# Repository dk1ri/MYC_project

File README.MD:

#The MYC Project 

MYC is a universal system to control hardware and software. A MYC system can merge different IOT systems and programms using a common user interface.

A MYC system contains skins and funcs (and a few other components)

A skin is a user interface, which can be selected and configured by the user - or a remote control or a simple switch.

A func is something, what can be controlled as a device or a program.

skin + func = App (or something similar)

The connection between skin and func is done by the (OSI layer 7) MYC protocol. The other OSI layer can be selected by demand.

MYC is not ready, you are invited to contribute

See also www.dk1ri.de

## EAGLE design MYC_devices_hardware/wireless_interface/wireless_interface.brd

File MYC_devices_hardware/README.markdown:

#MYC Hardware

Here some MYC hardware device are described.

All of them understand the MYC protocol. Some can be use a standalone equipment as well

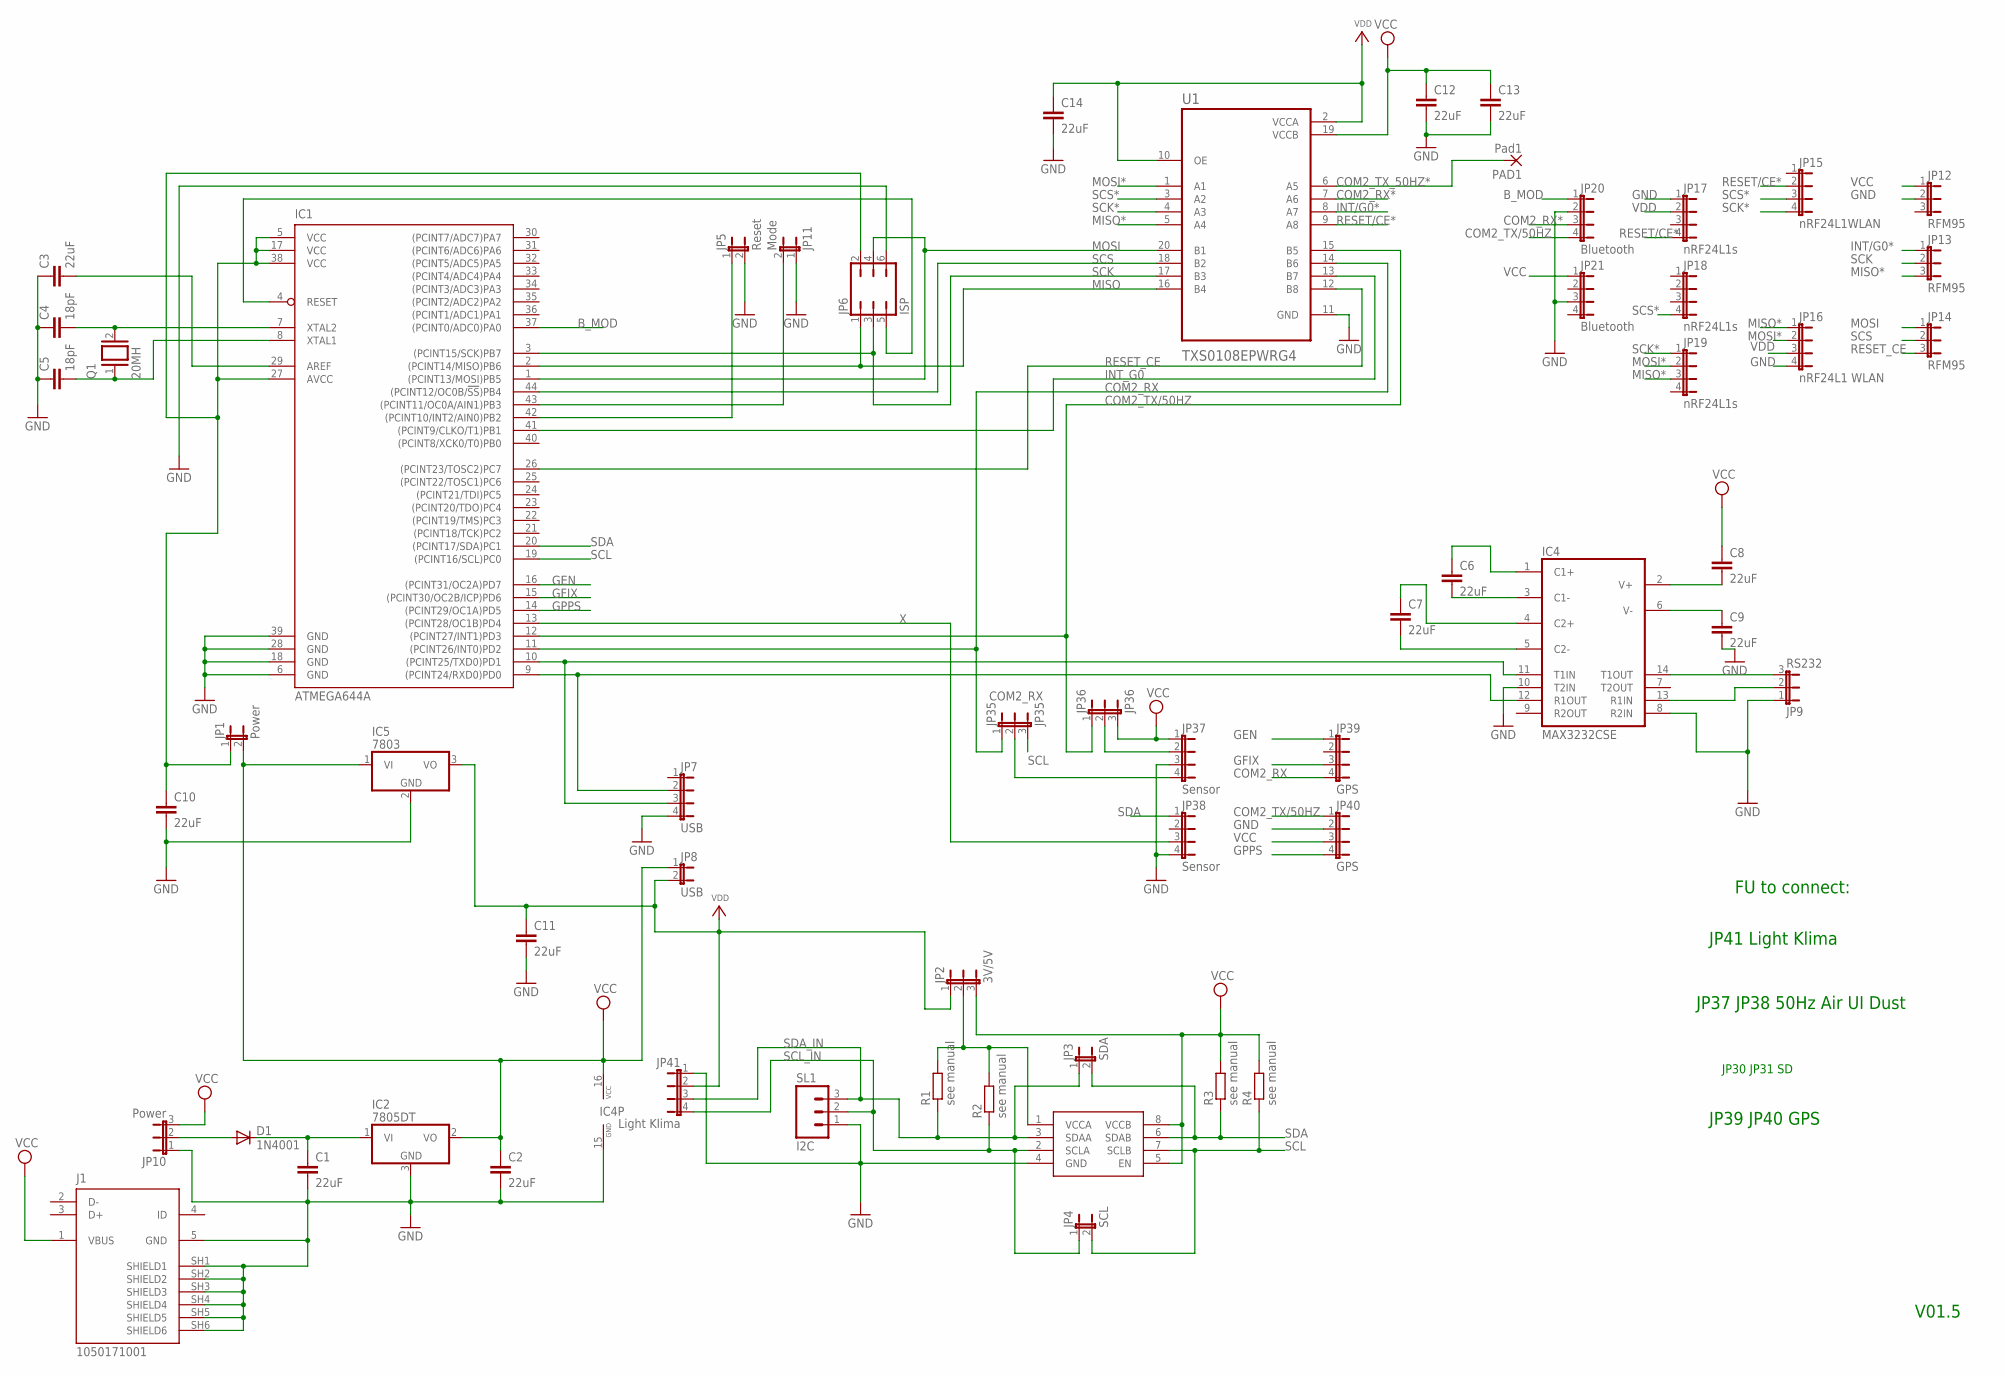
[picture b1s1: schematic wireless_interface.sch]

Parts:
C1, C2, C3, C6, C7, C8, C9, C10, C11, C12, C13, C14: 22uF; C1206
C4, C5: 18pF; C025-025X050
D1: 1N4001; SOD106-W
IC1: ATMEGA644A; TQFP44
IC2: 7805DT; TO252
IC3: PCA9517; SO-08
IC4: MAX3232CSE; SO16
IC5: 7803; TO220V
J1: 1050171001; MOLEX_1050171001
JP1: Power; JP1
JP2: 3V/5V; JP2
JP3: SDA; JP1
JP4: SCL; JP1
JP5: Reset; JP1
JP6: ISP; JP3Q
JP7: USB; JP4
JP8: USB; JP1
JP9: RS232; JP2
JP10: Power; JP2
JP11: Mode; JP1
JP12, JP13, JP14: RFM95; JP2
JP15: nRF24L1WLAN; JP4
JP16: nRF24L1 WLAN; JP4
JP17, JP18, JP19: nRF24L1s; JP4
JP20, JP21: Bluetooth; JP4
JP35: JP35; JP2
JP36: JP36; JP2
JP37, JP38: Sensor; JP4
JP39, JP40: GPS; JP4
JP41: Light Klima; JP4
PAD1: Pad1; SMD1,27-2,54
Q1: 20MH; QS
R1, R2, R3, R4: see manual; R1206
SL1: I2C; 03P
U1: TXS0108EPWRG4; SOP65P640X120-20N

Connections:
B_MOD: IC1.37 ((PCINT0/ADC0)PA0), JP20.1
COM2_RX: IC1.11 ((PCINT26/INT0)PD2), JP35.1, JP39.4, U1.14 (B6)
COM2_RX*: JP20.3, U1.7 (A6)
COM2_TX/50HZ: IC1.12 ((PCINT27/INT1)PD3), JP20.4, JP36.1, JP40.1, U1.15 (B5)
COM2_TX_50HZ*: PAD1.1, U1.6 (A5)
GEN: IC1.16 ((PCINT31/OC2A)PD7), JP39.1
GFIX: IC1.15 ((PCINT30/OC2B/ICP)PD6), JP39.3
GND: C1.2, C2.2, C3.1, C4.1, C5.1, C9.2, C10.2, C11.2, C12.2, C13.2, C14.2, IC1.6 (GND), IC1.18 (GND), IC1.28 (GND), IC1.39 (GND), IC2.3 (GND), IC3.4 (GND), IC4.8 (R2IN), IC4.10 (T2IN), IC4.15 (GND), IC5.2 (GND), J1.5 (GND), J1.SH1 (SHIELD1), J1.SH2 (SHIELD2), J1.SH3 (SHIELD3), J1.SH4 (SHIELD4), J1.SH5 (SHIELD5), J1.SH6 (SHIELD6), JP5.2, JP6.6, JP7.4, JP9.1, JP10.1, JP11.1, JP12.2, JP16.4, JP17.1, JP20.2, JP21.3, JP37.3, JP38.4, JP40.2, JP41.1, SL1.1, U1.11 (GND)
GPPS: IC1.14 ((PCINT29/OC1A)PD5), JP40.4
INT/G0*: JP13.1, U1.8 (A7)
INT_G0: IC1.41 ((PCINT9/CLKO/T1)PB1), U1.13 (B7)
MISO: IC1.2 ((PCINT14/MISO)PB6), JP6.1, U1.16 (B4)
MISO*: JP13.3, JP16.1, JP19.3, U1.5 (A4)
MOSI: IC1.1 ((PCINT13/MOSI)PB5), JP6.4, JP14.1, U1.20 (B1)
MOSI*: JP16.2, JP19.2, U1.1 (A1)
unnamed: JP36.2, JP37.2
unnamed: C10.1, IC1.5 (VCC), IC1.17 (VCC), IC1.27 (AVCC), IC1.38 (VCC), JP1.1, JP6.2
unnamed: IC4.13 (R1IN), JP9.2
unnamed: IC1.9 ((PCINT24/RXD0)PD0), IC4.12 (R1OUT), JP7.2
unnamed: IC1.42 ((PCINT10/INT2/AIN0)PB2), JP5.1
unnamed: IC1.43 ((PCINT11/OC0A/AIN1)PB3), JP11.2
unnamed: C6.1, IC4.1 (C1+)
unnamed: C6.2, IC4.3 (C1-)
unnamed: C7.1, IC4.4 (C2+)
unnamed: C7.2, IC4.5 (C2-)
unnamed: D1.A, JP10.2
unnamed: C8.2, IC4.2 (V+)
unnamed: C3.2, IC1.29 (AREF)
unnamed: C9.1, IC4.6 (V-)
unnamed: IC4.14 (T1OUT), JP9.3
unnamed: JP35.2, JP37.4
unnamed: IC1.4 (RESET), JP6.5
unnamed: C4.2, IC1.7 (XTAL2), Q1.2
unnamed: IC1.10 ((PCINT25/TXD0)PD1), IC4.11 (T1IN), JP7.3
unnamed: C1.1, D1.C, IC2.1 (VI)
unnamed: C5.2, IC1.8 (XTAL1), Q1.1
unnamed: IC3.1 (VCCA), JP2.2, R1.2, R2.2
RESET/CE*: JP15.2, JP17.4, U1.9 (A8)
RESET_CE: IC1.26 ((PCINT23/TOSC2)PC7), JP14.3, U1.12 (B8)
SCK: IC1.3 ((PCINT15/SCK)PB7), JP6.3, JP13.2, U1.17 (B3)
SCK*: JP15.4, JP19.1, U1.4 (A3)
SCL: IC1.19 ((PCINT16/SCL)PC0), IC3.7 (SCLB), JP4.2, JP35.3, R4.1
SCL_IN: IC3.2 (SCLA), JP4.1, JP41.4, R2.1, SL1.2
SCS: IC1.44 ((PCINT12/OC0B/!SS!)PB4), JP14.2, U1.18 (B2)
SCS*: JP15.3, JP18.4, U1.3 (A2)
SDA: IC1.20 ((PCINT17/SDA)PC1), IC3.6 (SDAB), JP3.2, JP38.1, R3.1
SDA_IN: IC3.3 (SDAA), JP3.1, JP41.3, R1.1, SL1.3
VCC: C2.1, C8.1, C12.1, C13.1, IC2.2 (VO), IC3.5 (EN), IC3.8 (VCCB), IC4.16 (VCC), IC5.1 (VI), J1.1 (VBUS), JP1.2, JP2.3, JP8.1, JP10.3, JP12.1, JP21.1, JP36.3, JP37.1, JP40.3, R3.2, R4.2, U1.19 (VCCB)
VDD: C11.1, C14.1, IC5.3 (VO), JP2.1, JP8.2, JP16.3, JP17.2, JP41.2, U1.2 (VCCA), U1.10 (OE)
X: IC1.13 ((PCINT28/OC1B)PD4), JP38.3

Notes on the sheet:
V01.5
FU to connect:
JP37 JP38 50Hz Air UI Dust
JP41 Light Klima
JP30 JP31 SD
JP39 JP40 GPS

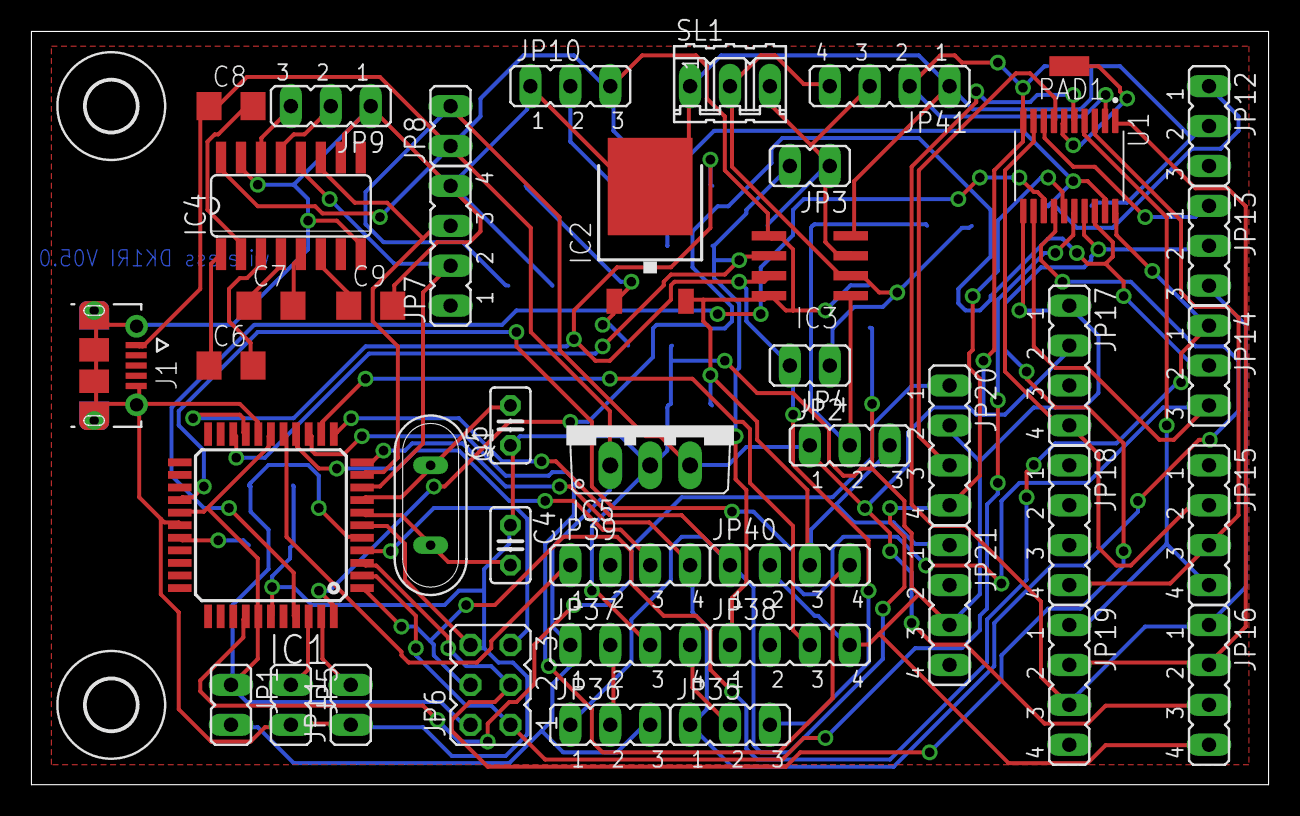
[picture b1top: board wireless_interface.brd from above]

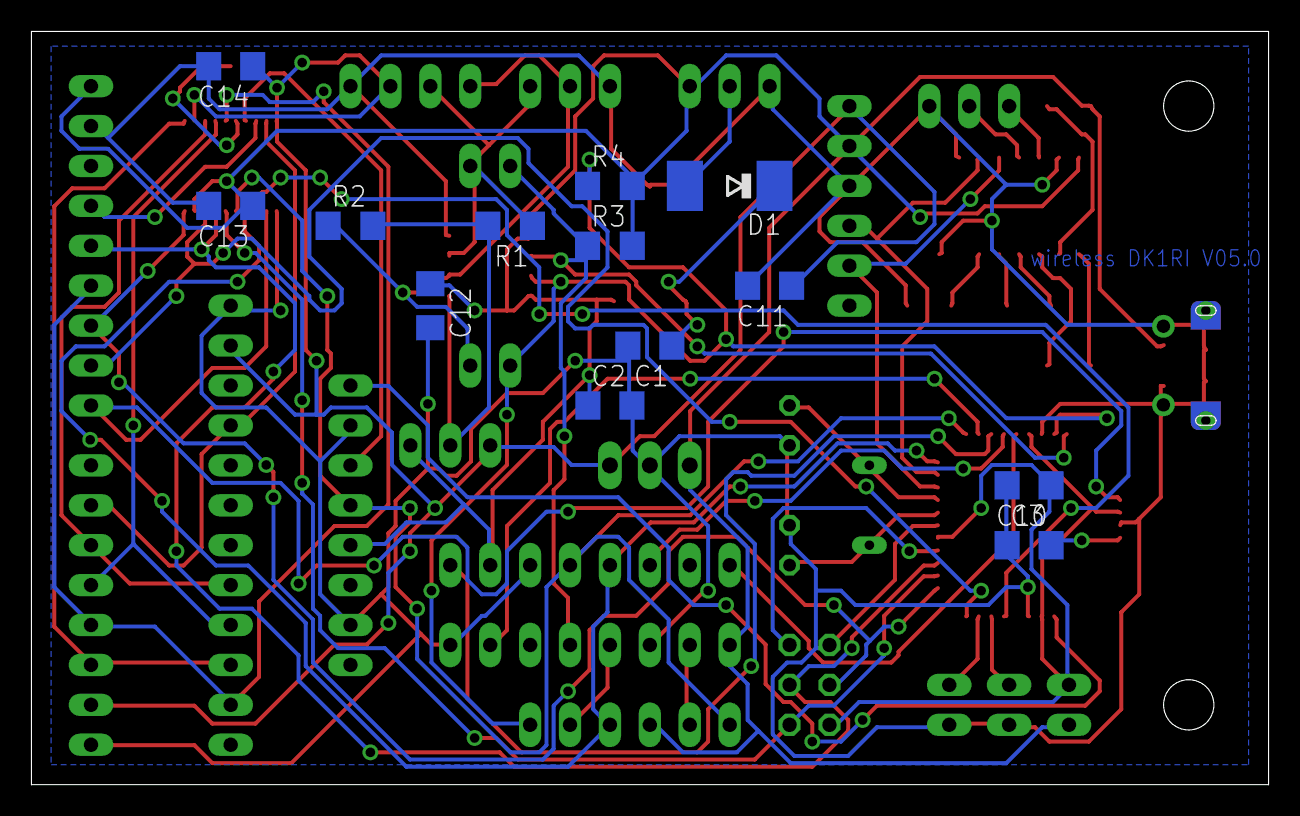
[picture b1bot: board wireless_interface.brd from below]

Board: 2 copper layers, 78.7 x 47.9 mm, 59 parts (13 on the bottom side), 50 nets.

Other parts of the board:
U$3, U$5: 3,2

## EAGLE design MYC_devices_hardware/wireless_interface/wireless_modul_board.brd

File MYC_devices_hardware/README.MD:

#MYC Hardware

Here some MYC hardware devices are described.

All of them understand the MYC protocol. Some can be used as standalone equipment as well

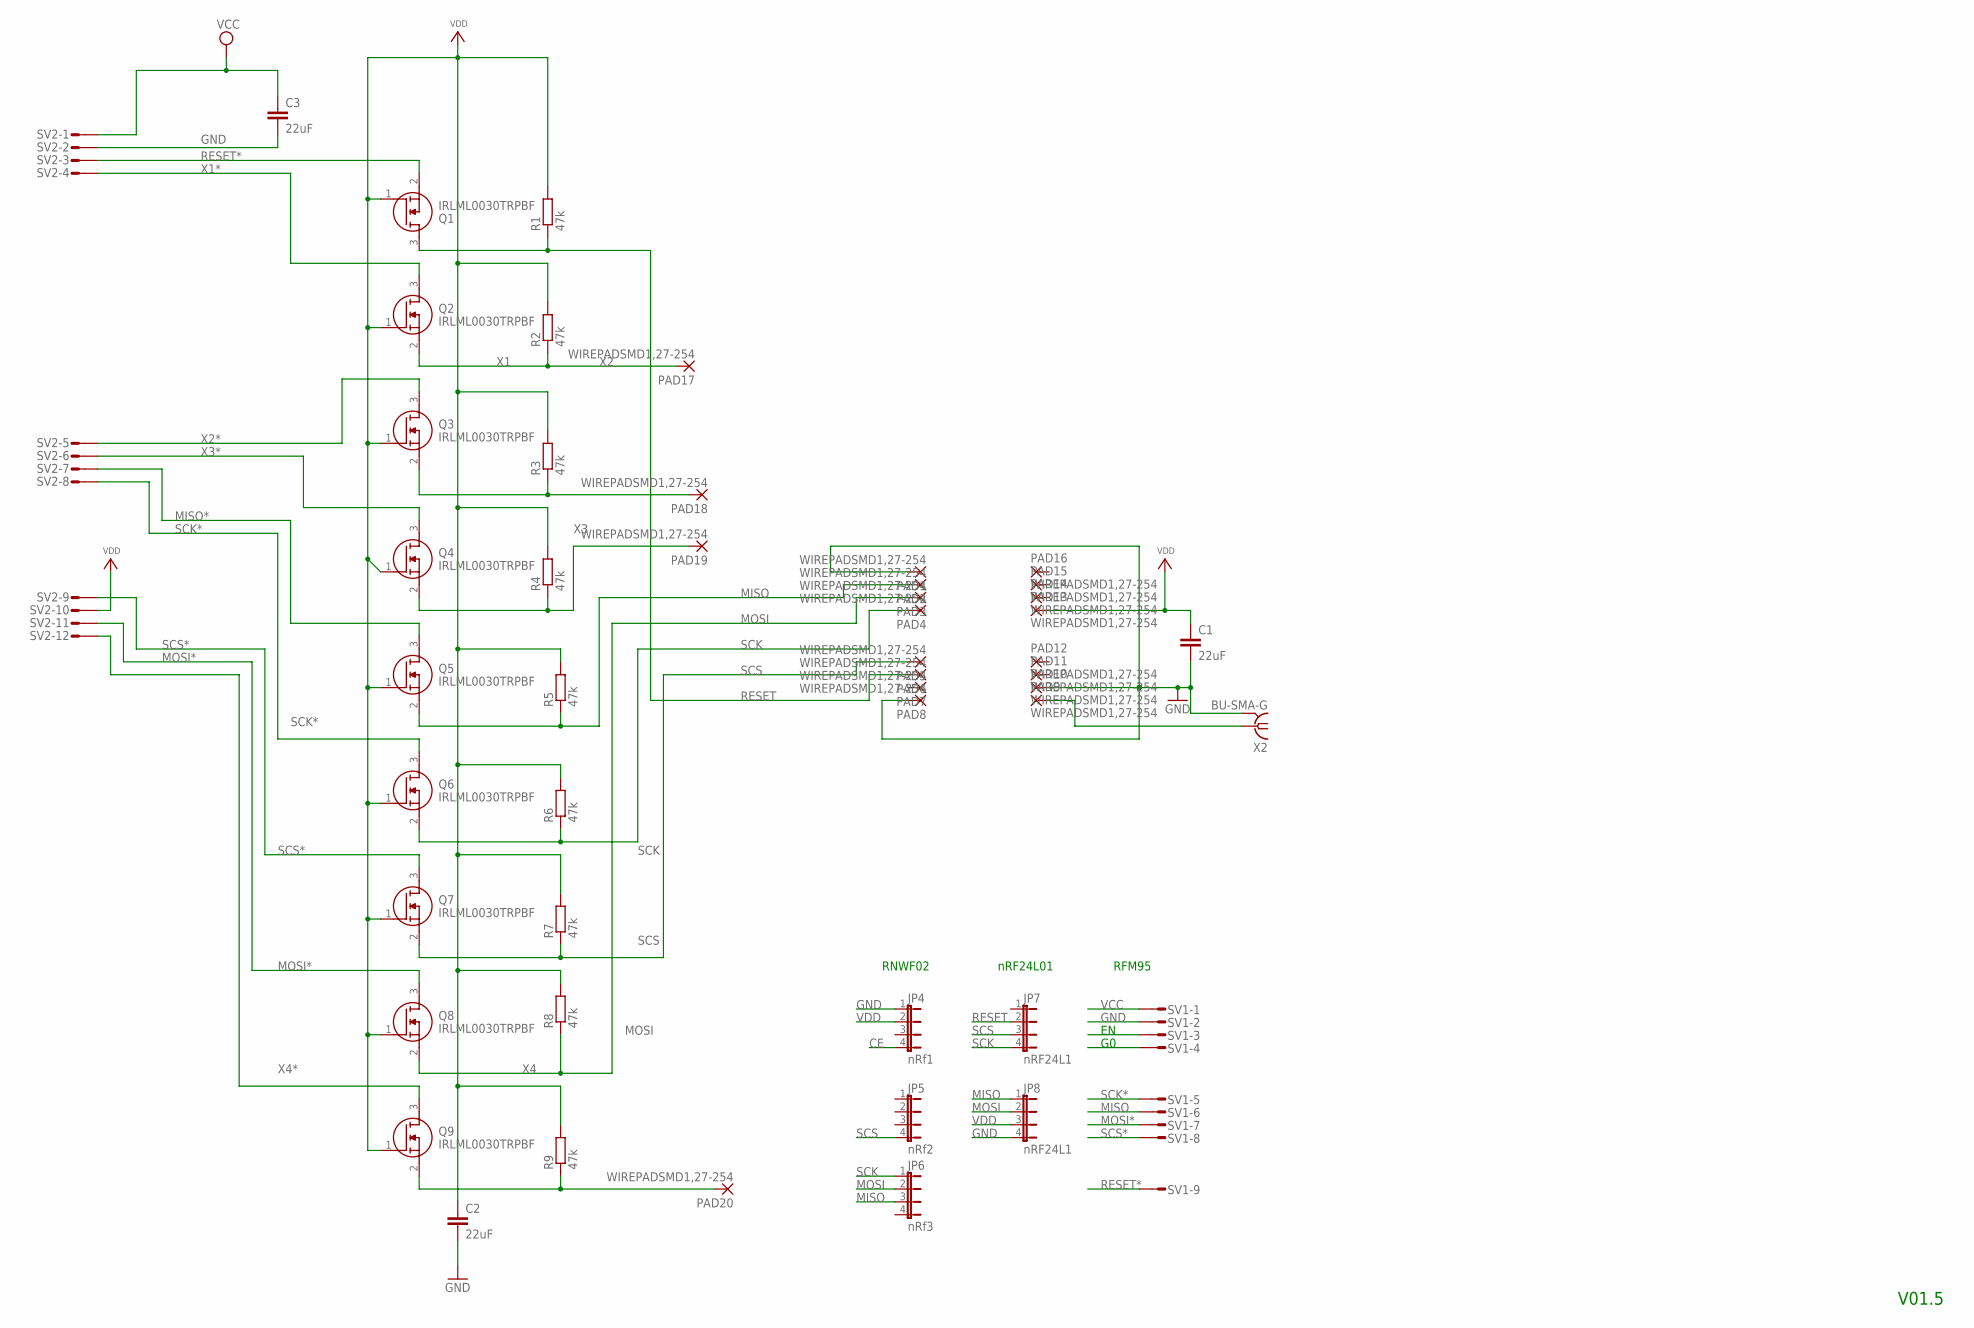
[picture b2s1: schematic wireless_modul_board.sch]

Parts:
C1, C2, C3: 22uF; C1206
JP4: nRf1; JP4
JP5: nRf2; JP4
JP6: nRf3; JP4
JP7, JP8: nRF24L1; JP4
PAD1, PAD2, PAD3, PAD4, PAD5, PAD6, PAD7, PAD8, PAD9, PAD10, PAD11, PAD12, PAD13, PAD14, PAD15, PAD16, PAD17, PAD18, PAD19, PAD20: WIREPADSMD1,27-254; SMD1,27-2,54
Q1, Q2, Q3, Q4, Q5, Q6, Q7, Q8, Q9: IRLML0030TRPBF; SOT95P237X112-3N
R1, R2, R3, R4, R5, R6, R7, R8, R9: 47k; R1206
SV1: S09P
SV2: S12P
X2: BU-SMA-G

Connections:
CE: JP4.4
GND: C1.2, C2.2, C3.2, JP4.1, JP8.4, PAD1.1, PAD8.1, PAD10.1, SV1.2, SV2.2, X2.2, X2.3 (2), X2.4 (2), X2.5 (2)
MISO: JP6.3, JP8.1, PAD2.1, Q5.2 (S), R5.1, SV1.6
MISO*: Q5.3 (D), SV2.7
MOSI: JP6.2, JP8.2, PAD3.1, Q8.2 (S), R8.1
MOSI*: Q8.3 (D), SV1.7, SV2.11
unnamed: PAD9.1, X2.1
RESET: JP7.2, PAD6.1, Q1.3 (D), R1.1
RESET*: Q1.2 (S), SV1.9, SV2.3
SCK: JP6.1, JP7.4, PAD4.1, Q6.2 (S), R6.1
SCK*: Q6.3 (D), SV1.5, SV2.8
SCS: JP5.4, JP7.3, PAD5.1, Q7.2 (S), R7.1
SCS*: Q7.3 (D), SV1.8, SV2.9
VCC: C3.1, SV1.1, SV2.1
VDD: C1.1, C2.1, JP4.2, JP8.3, PAD13.1, Q1.1 (G), Q2.1 (G), Q3.1 (G), Q4.1 (G), Q5.1 (G), Q6.1 (G), Q7.1 (G), Q8.1 (G), Q9.1 (G), R1.2, R2.2, R3.2, R4.2, R5.2, R6.2, R7.2, R8.2, R9.2, SV2.10
X1: PAD17.1, Q2.2 (S), R2.1
X1*: Q2.3 (D), SV2.4
X2: PAD18.1, Q3.2 (S), R3.1
X2*: Q3.3 (D), SV2.5
X3: PAD19.1, Q4.2 (S), R4.1
X3*: Q4.3 (D), SV2.6
X4: PAD20.1, Q9.2 (S), R9.1
X4*: Q9.3 (D), SV2.12

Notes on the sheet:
V01.5
nRF24L01
RNWF02
RFM95

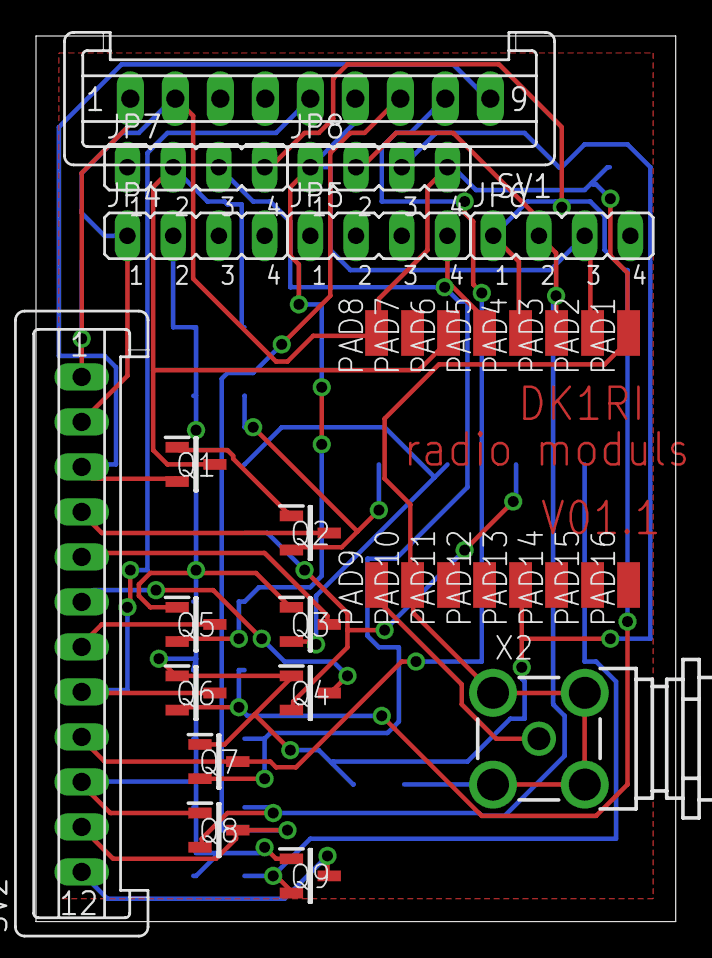
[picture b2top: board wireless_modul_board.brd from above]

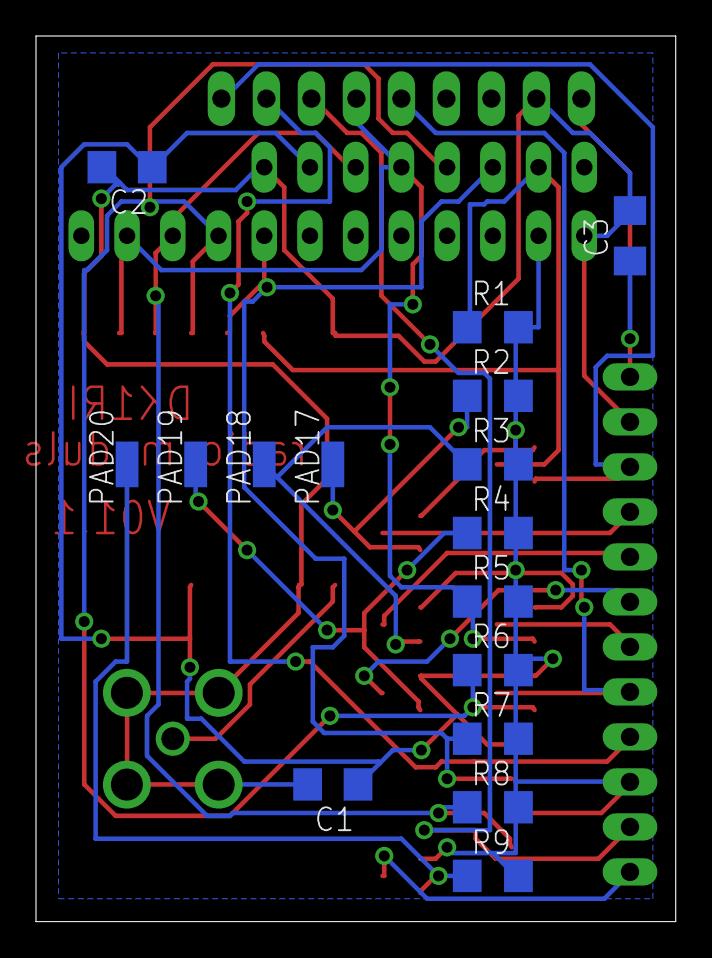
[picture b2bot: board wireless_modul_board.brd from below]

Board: 2 copper layers, 35.5 x 49.2 mm, 49 parts (16 on the bottom side), 22 nets.

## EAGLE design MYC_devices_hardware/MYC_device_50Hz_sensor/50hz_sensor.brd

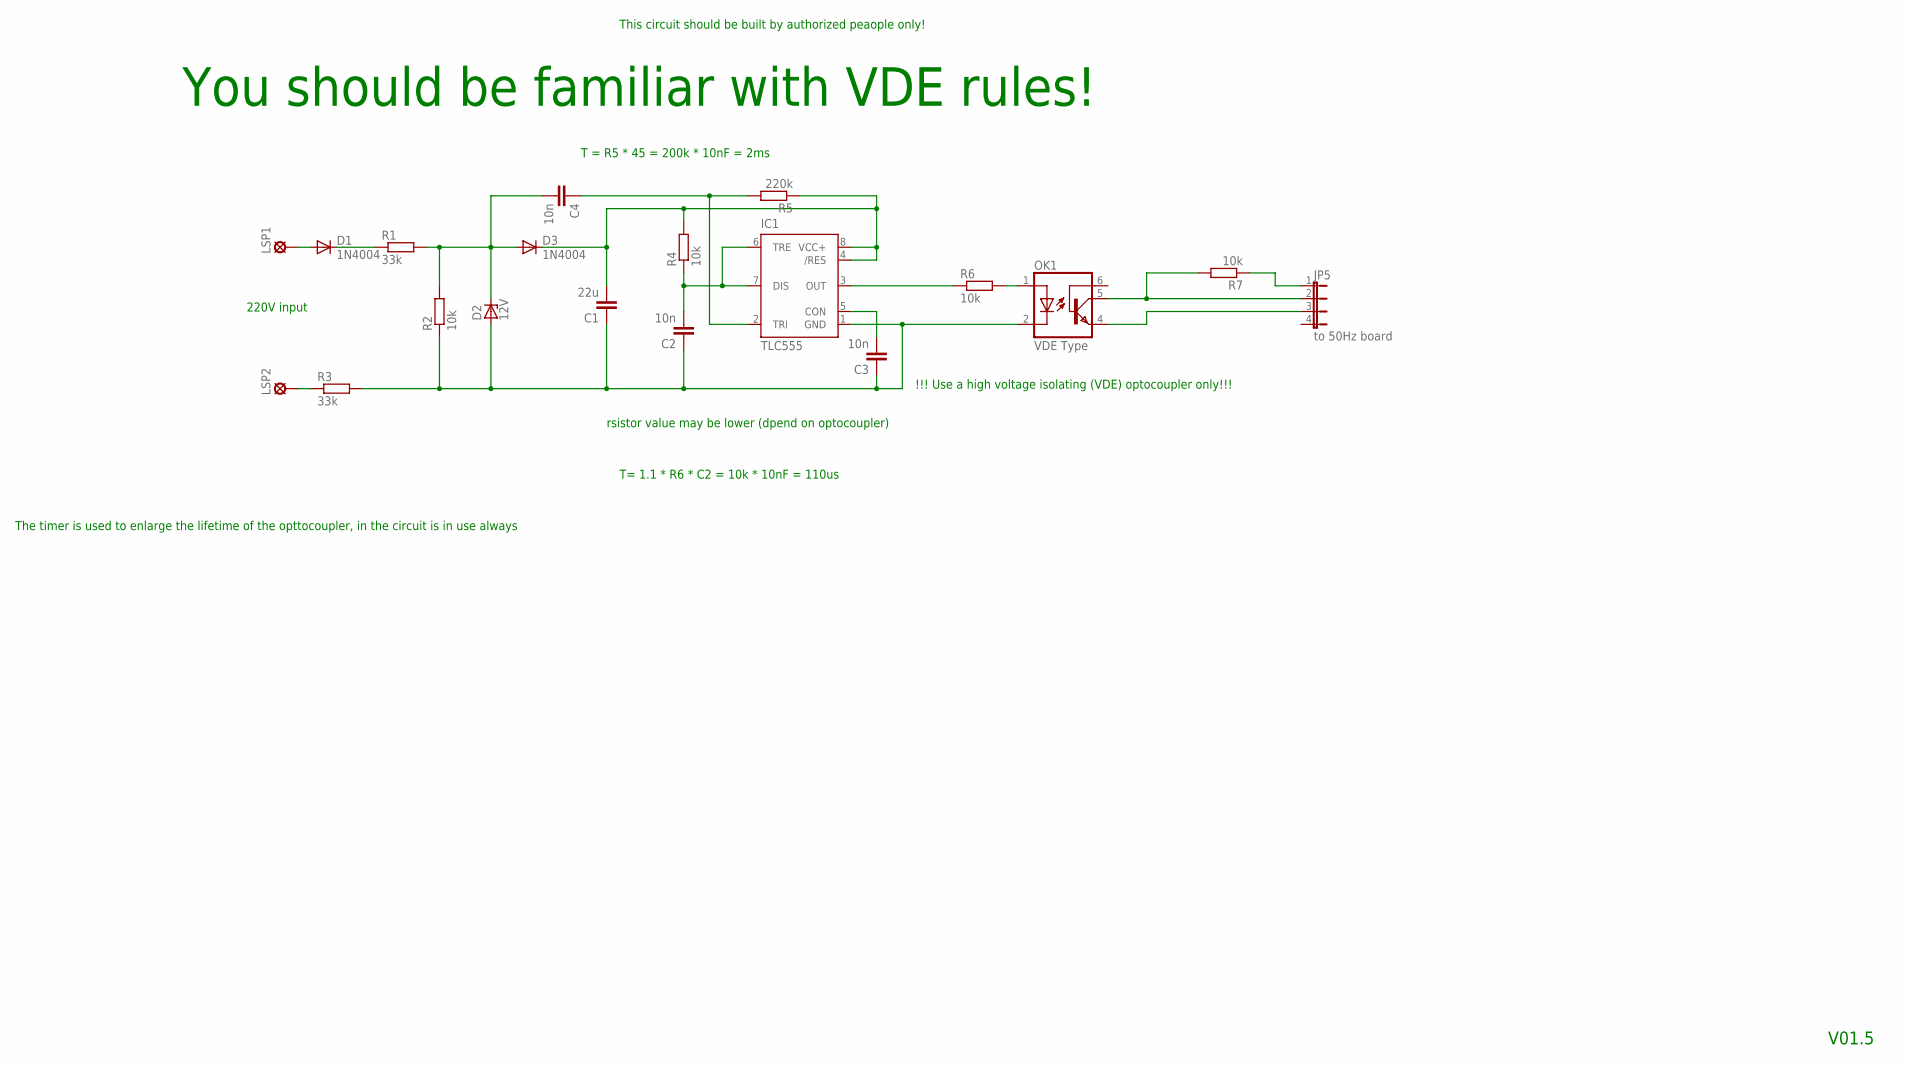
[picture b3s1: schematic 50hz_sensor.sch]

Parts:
C1: 22u; C025-040X050
C2: 10n; C050-025X075
C3: 10n; C050-035X075
C4: 10n; C050-030X075
D1, D3: 1N4004; DO41-10
D2: 12V; DO34Z7
IC1: TLC555; DIL-08
JP5: to 50Hz board; JP4
LSP1, LSP2: LSP11
OK1: VDE Type; DIL6-04
R1, R3: 33k; 0309/10
R2, R4, R6, R7: 10k; 0309/10
R5: 220k; 0309/10

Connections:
unnamed: D1.A, LSP1.MP
unnamed: LSP2.MP, R3.1
unnamed: JP5.2, OK1.5 (COL), R7.2
unnamed: OK1.1 (A), R6.2
unnamed: C1.1, C2.1, C3.1, D2.A, IC1.1 (GND), OK1.2 (C), R2.1, R3.2
unnamed: D1.C, R1.1
unnamed: C4.1, IC1.2 (TRI), R5.2
unnamed: JP5.3, OK1.4 (EMI)
unnamed: JP5.1, R7.1
unnamed: C1.2, D3.C, IC1.4 (/RES), IC1.8 (VCC+), R4.2, R5.1
unnamed: IC1.3 (OUT), R6.1
unnamed: C2.2, IC1.6 (TRE), IC1.7 (DIS), R4.1
unnamed: C3.2, IC1.5 (CON)
unnamed: C4.2, D2.C, D3.A, R1.2, R2.2

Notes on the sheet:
V01.5
220V input
This circuit should be built by authorized peaople only!
You should be familiar with VDE rules!
!!! Use a high voltage isolating (VDE) optocoupler only!!!
rsistor value may be lower (dpend on optocoupler)
T= 1.1 * R6 * C2 = 10k * 10nF = 110us
The timer is used to enlarge the lifetime of the opttocoupler, in the circuit is in use always
T = R5 * 45 = 200k * 10nF = 2ms

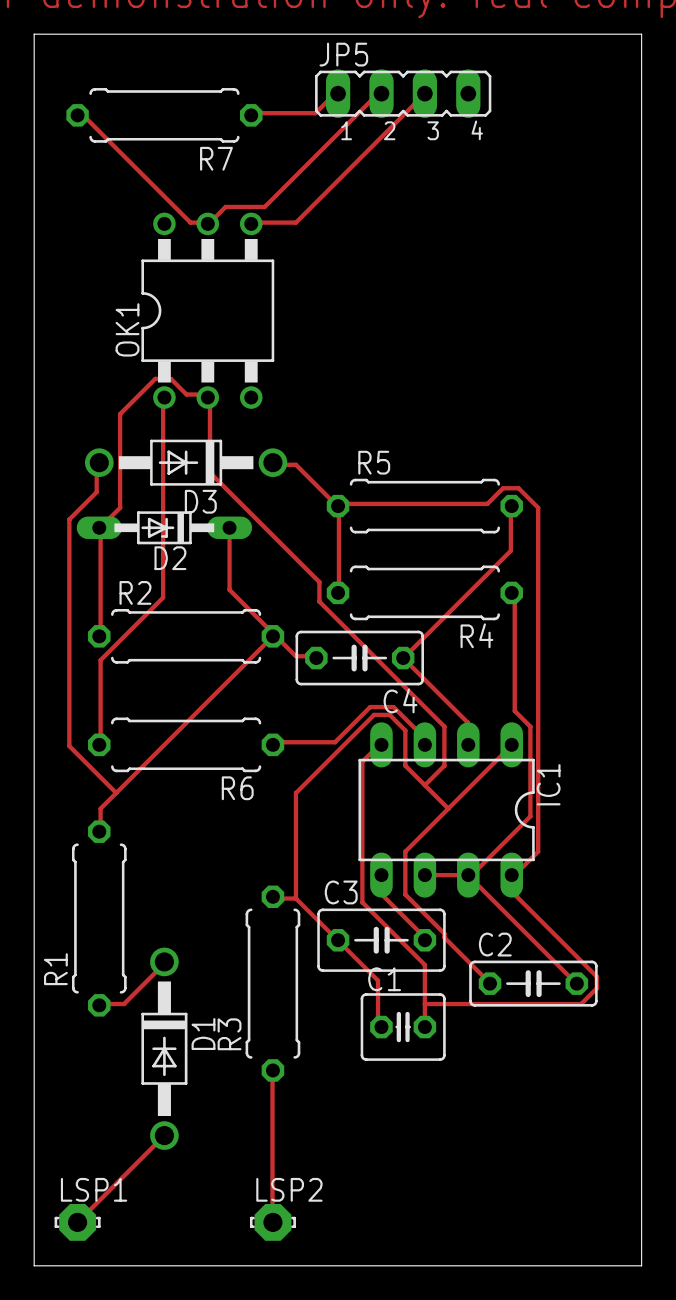
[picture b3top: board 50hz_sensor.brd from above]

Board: 2 copper layers, 35.5 x 72.1 mm, 19 parts (0 on the bottom side), 14 nets.

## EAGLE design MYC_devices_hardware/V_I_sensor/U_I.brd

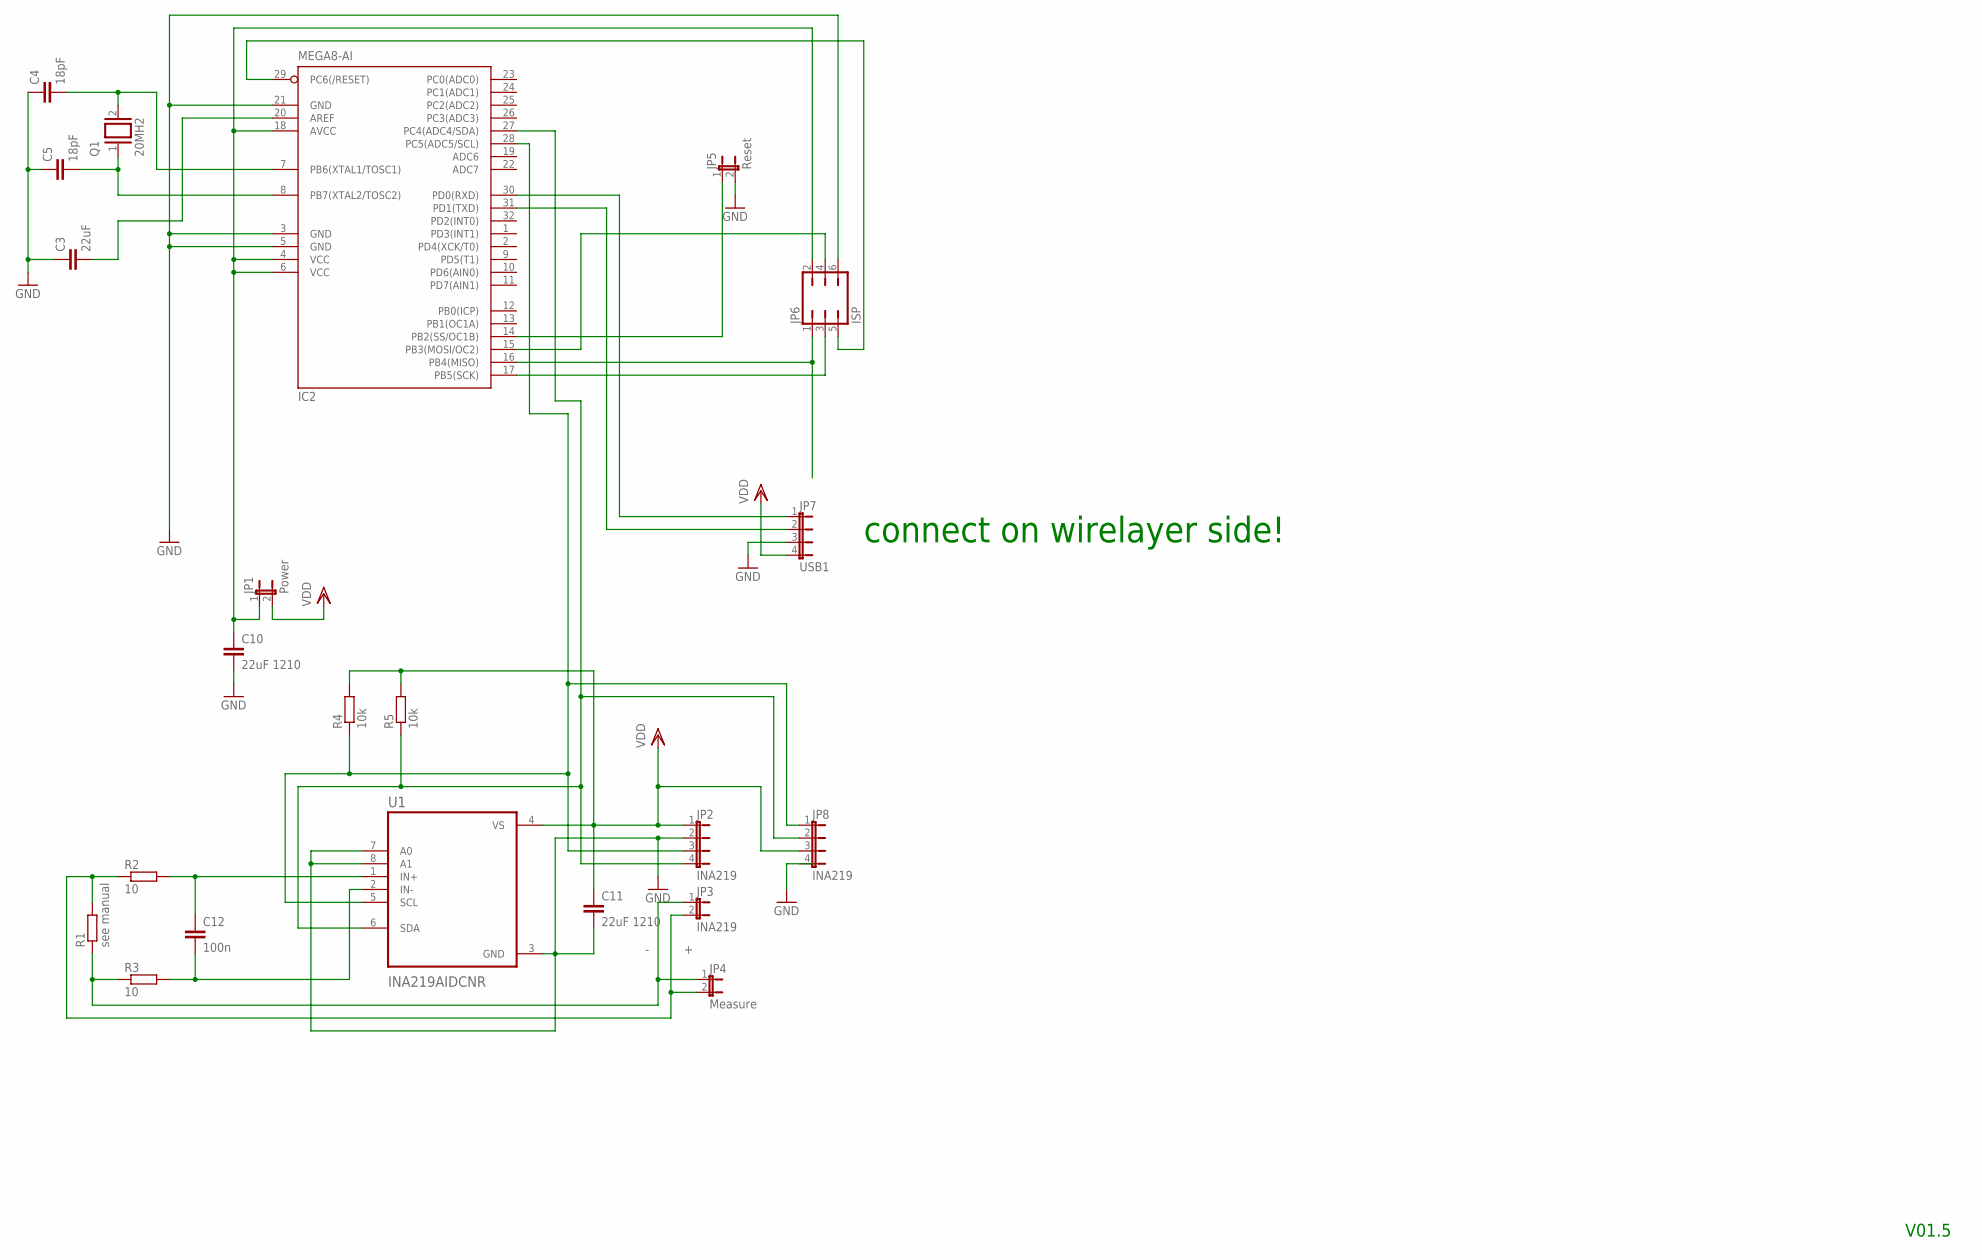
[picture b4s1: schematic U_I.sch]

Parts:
C3: 22uF; C1206
C4, C5: 18pF; C025-025X050
C10, C11: 22uF 1210; C1206
C12: 100n; C1206
IC2: MEGA8-AI; TQFP32-08
JP1: Power; JP1
JP2, JP8: INA219; JP4
JP3: INA219; JP1
JP4: Measure; JP1
JP5: Reset; JP1
JP6: ISP; JP3Q
JP7: USB1; JP4
Q1: 20MH2; QS
R1: see manual; R1210
R2, R3: 10; R1206
R4, R5: 10k; R1206
U1: INA219AIDCNR; SOT65P280X145-8N

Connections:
+: JP3.2, JP4.2, R1.2, R2.1
-: JP3.1, JP4.1, R1.1, R3.1
GND: C3.1, C4.1, C5.1, C10.2, C11.2, IC2.3 (GND), IC2.5 (GND), IC2.21 (GND), JP2.2, JP5.2, JP6.6, JP7.3, U1.3 (GND), U1.7 (A0), U1.8 (A1)
unnamed: C12.1, R2.2, U1.1 (IN+)
unnamed: IC2.31 (PD1(TXD)), JP7.2
unnamed: IC2.16 (PB4(MISO)), JP6.1
unnamed: IC2.27 (PC4(ADC4/SDA)), JP2.4, JP8.2, R5.1, U1.6 (SDA)
unnamed: C10.1, IC2.4 (VCC), IC2.6 (VCC), IC2.18 (AVCC), JP1.1, JP6.2
unnamed: C4.2, IC2.7 (PB6(XTAL1/TOSC1)), Q1.2
unnamed: IC2.15 (PB3(MOSI/OC2)), JP6.4
unnamed: IC2.30 (PD0(RXD)), JP7.1
unnamed: IC2.14 (PB2(SS/OC1B)), JP5.1
unnamed: IC2.29 (PC6(/RESET)), JP6.5
unnamed: C12.2, R3.2, U1.2 (IN-)
unnamed: C5.2, IC2.8 (PB7(XTAL2/TOSC2)), Q1.1
unnamed: IC2.28 (PC5(ADC5/SCL)), JP2.3, JP8.1, R4.1, U1.5 (SCL)
unnamed: C3.2, IC2.20 (AREF)
unnamed: IC2.17 (PB5(SCK)), JP6.3
VDD: C11.1, JP1.2, JP2.1, JP7.4, JP8.3, R4.2, R5.2, U1.4 (VS)

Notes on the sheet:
V01.5
connect on wirelayer side!

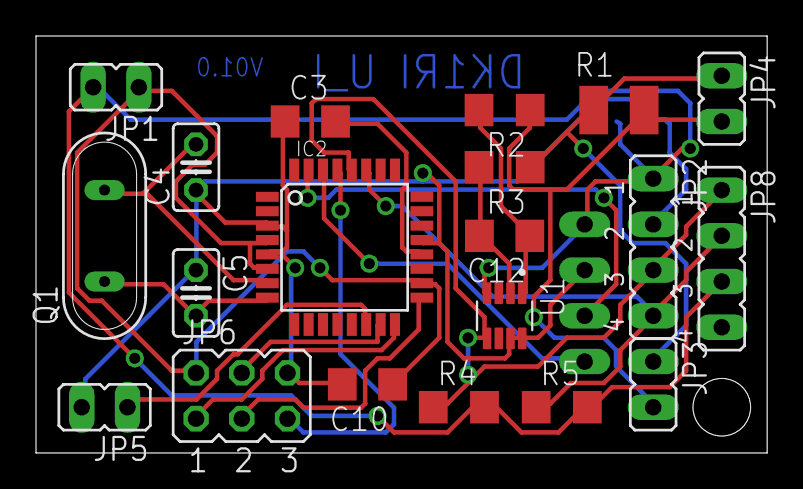
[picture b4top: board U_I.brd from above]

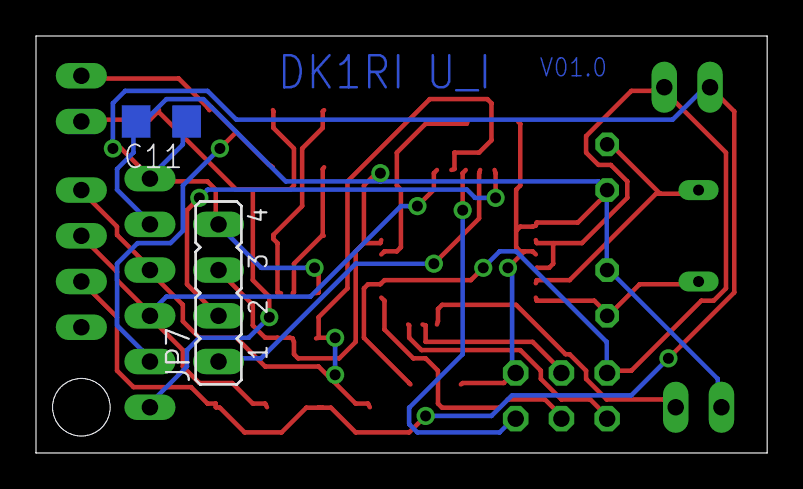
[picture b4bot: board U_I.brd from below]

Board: 2 copper layers, 40.6 x 23.2 mm, 22 parts (2 on the bottom side), 19 nets.
